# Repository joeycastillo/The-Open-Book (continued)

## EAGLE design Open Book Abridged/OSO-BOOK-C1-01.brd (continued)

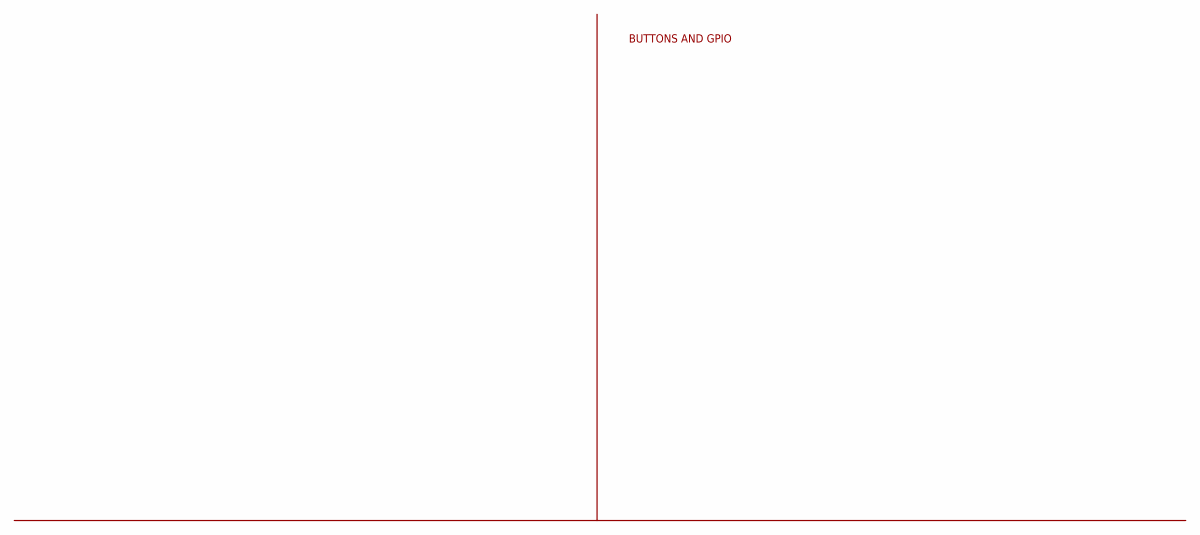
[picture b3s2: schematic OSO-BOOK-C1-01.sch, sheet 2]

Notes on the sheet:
BUTTONS AND GPIO

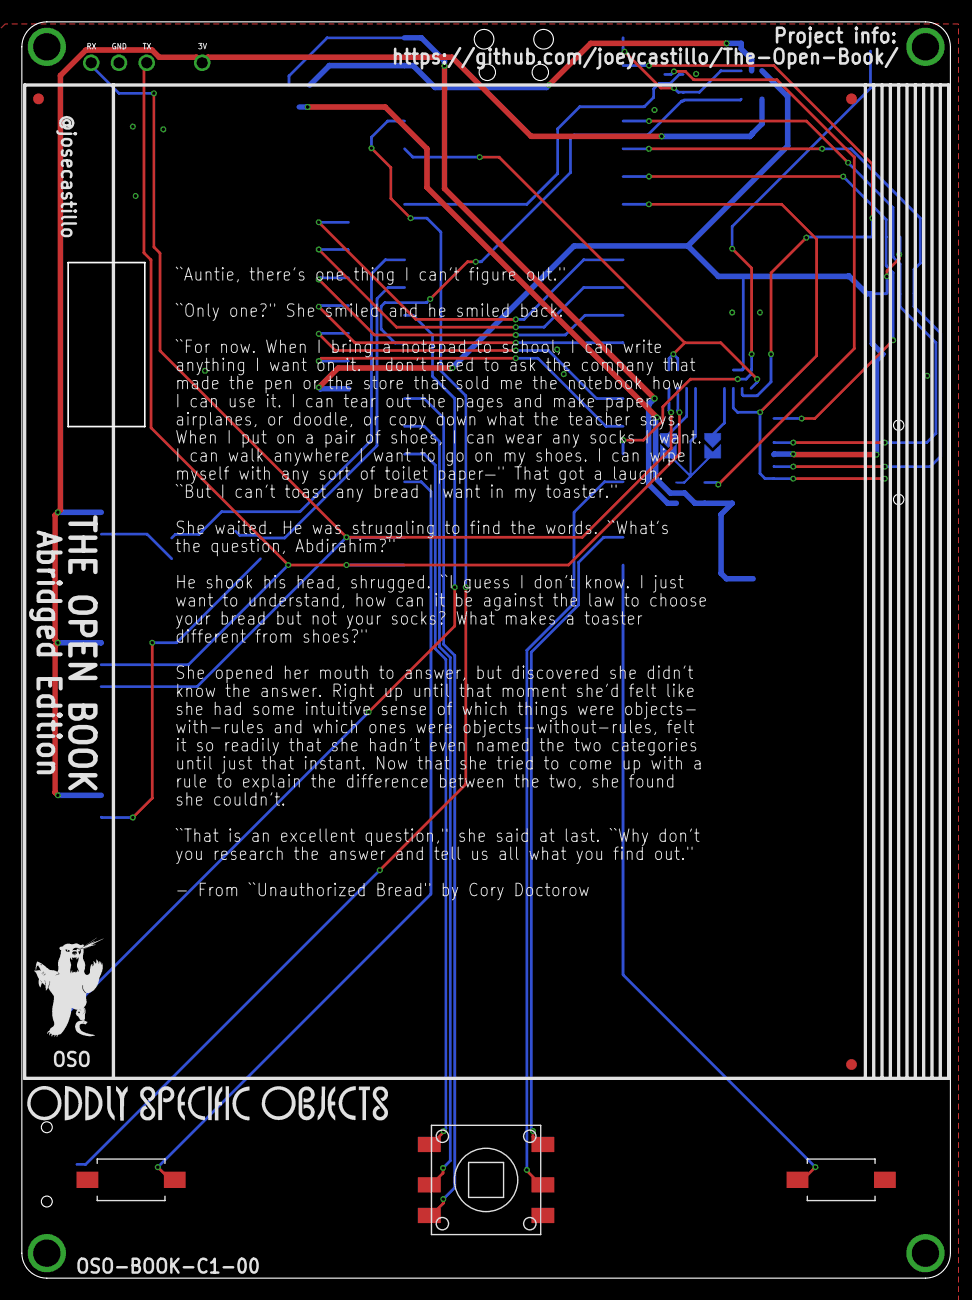
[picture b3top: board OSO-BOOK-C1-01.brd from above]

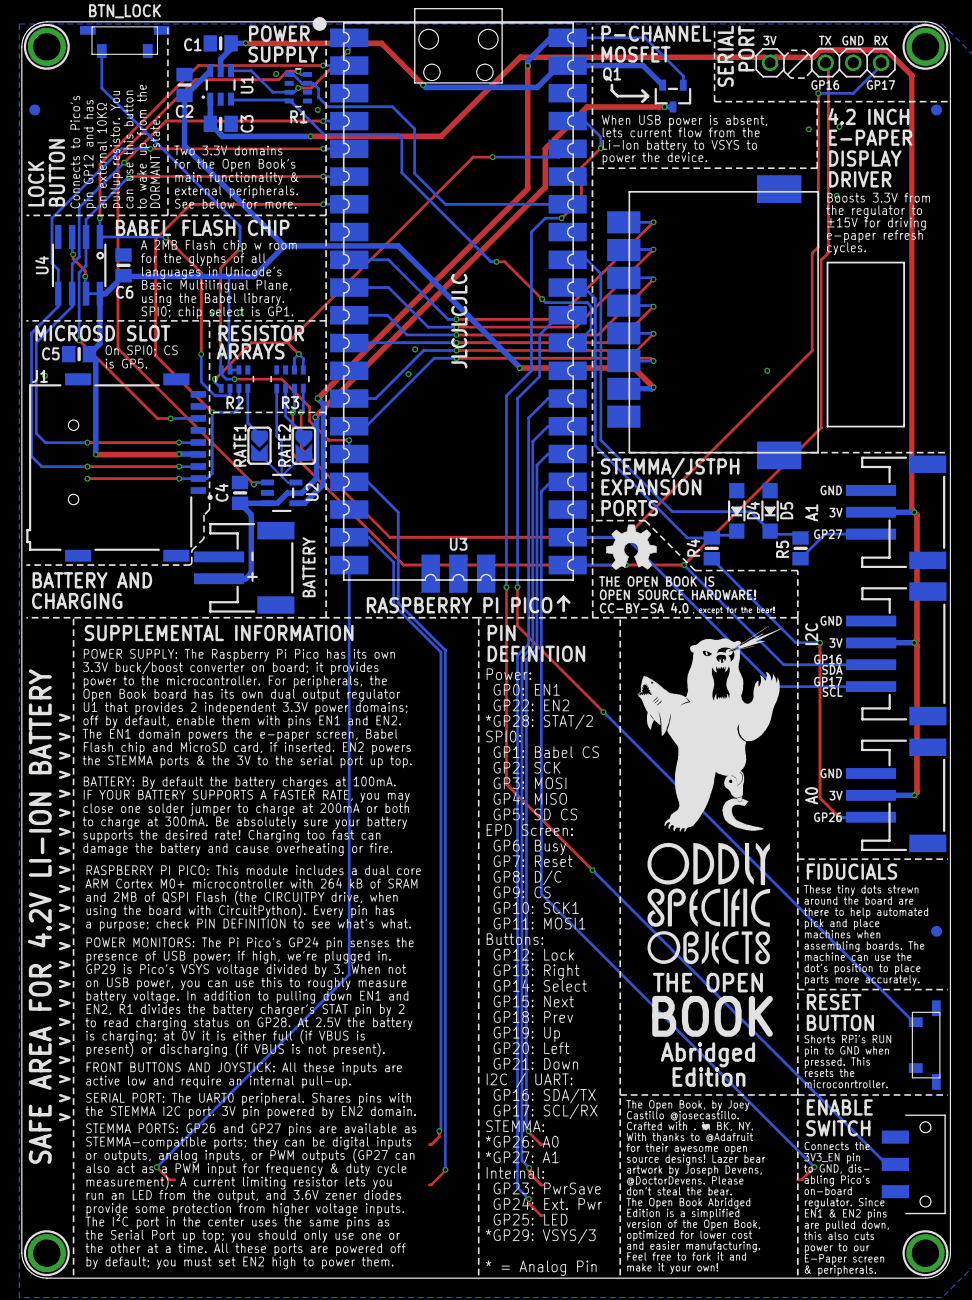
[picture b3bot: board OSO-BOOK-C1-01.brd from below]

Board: 2 copper layers, 85.0 x 115.0 mm, 49 parts (41 on the bottom side), 41 nets.

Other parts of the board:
U$45: OSO_WORDMARK_125X1300MIL_1000DPI
U$47: OSO_BEAR_525X750MIL_1000DPI
U$49: OSO_WORDMARK_THREELINE_450MIL_1000DPI
U$65: OSO_BEAR_250X360MIL_1000DPI

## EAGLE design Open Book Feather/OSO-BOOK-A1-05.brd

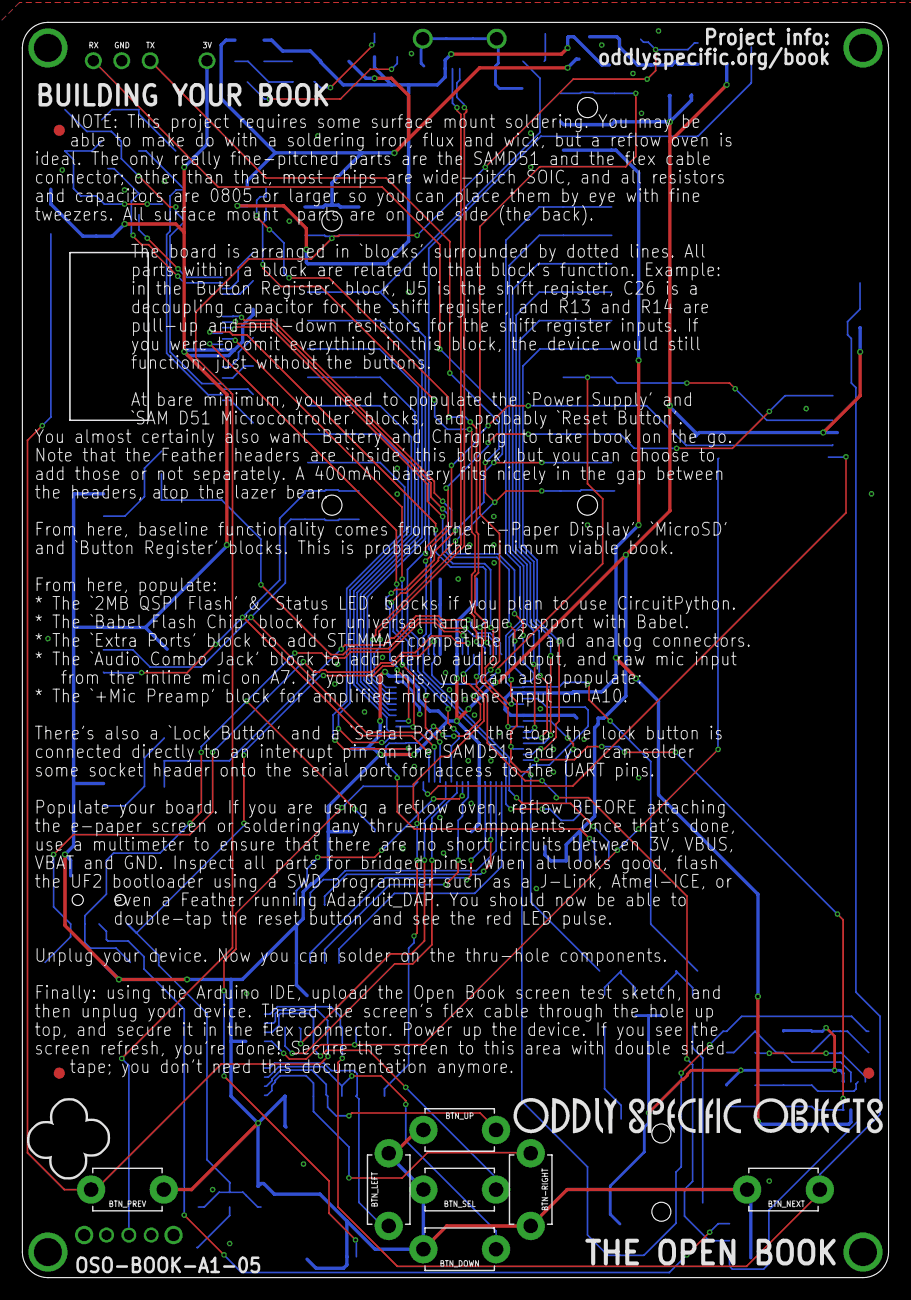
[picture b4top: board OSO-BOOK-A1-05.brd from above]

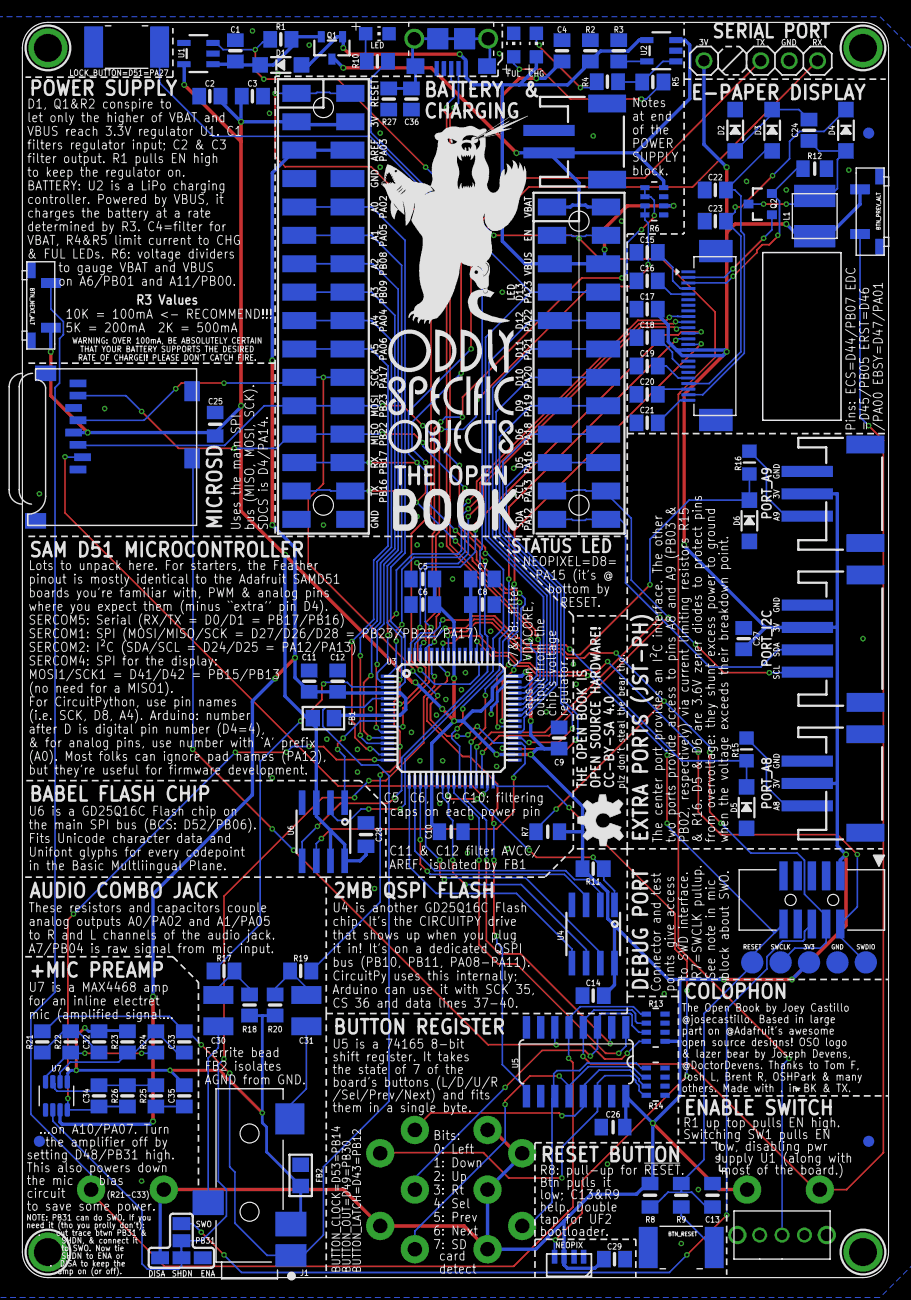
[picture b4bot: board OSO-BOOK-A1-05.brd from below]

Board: 2 copper layers, 77.5 x 112.3 mm, 130 parts (117 on the bottom side), 100 nets.

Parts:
BTN-RIGHT: TACT_PANA-EVQ
BTN_DOWN: TACT_PANA-EVQ
BTN_LEFT: TACT_PANA-EVQ
BTN_LOCK: BTN_CK_KSS
BTN_NEXT: TACT_PANA-EVQ
BTN_PREV: TACT_PANA-EVQ
BTN_RESET: BTN_CK_KSS
BTN_SEL: TACT_PANA-EVQ
BTN_UP: TACT_PANA-EVQ
C1, C2, C4, C11: 10µF; 0805-NO
C3, C9, C12, C14, C15, C16, C17, C29: 1uF; 0805-NO
C5, C7, C25: 10uF; 0805_10MGAP
C6, C8, C10, C26, C28: 1uF; 0805_10MGAP
C13: 0.1uF; 0805_10MGAP
C18, C19, C20, C21, C22, C23: 1uF/25V; 0805-NO
C24: 4.7uF/25V; 0805-NO
C27, C35: 10uF; 0805-NO
C30, C31: 100uF; C1210
C32: 0.1µF; 0805-NO
C33: 0.01uF; 0805-NO
C34: 100pF; 0805-NO
C36: 4.5nF; 0805-NO
CHG: AMBER; CHIP-LED0805
D1: MBR120; SOD-123
D2, D3, D4: MBR0530; SOD-123
D5, D6: 3.6V; SOD-123
DNP_NEXT_ALT: SPST_TACTILE_SWITCHRA; TL3330AF130QG
DNP_PREV_ALT: SPST_TACTILE_SWITCHRA; TL3330AF130QG
FB1, FB2: Ferrite; 0805
FID1, FID2, FID3, FID4, FID5, FID6: FIDUCIAL_1MM
FUL: GREEN; CHIP-LED0805
GOLD_ORB_SM1: OSHWLOGOLOGO5MM; OSHW_5MM
J1: SJ-43514-SMT; CUI_SJ-43514-SMT
J2: 10118193-0001LF; FCI_10118193-0001LF
JP1: 1X03
JP2: 1X01
L1: 10uH; MICROBUILDER_INDUCTOR_4X4MM_NR401_BIGPADS
LED: RED; CHIP-LED0805
MICROSD: MICROSD
MS1: FEATHERWING_SMTDUAL; FEATHERWING_SMT2
NEOPIX: WS2812B_4020
PORT_A8, PORT_A9: JST PH 3; JSTPH3
PORT_I2C: JST PH 4; JSTPH4
Q1: DMG341; SOT23-R
Q2: IRLML0100; SOT23-3
R1, R3: 10K; 0805-NO
R2, R11, R26: 100K; 0805-NO
R4, R5, R10, R21, R22, R25: 1K; 0805-NO
R6, R13, R14: 100K; EXBV8V
R7, R8: 10K; 0805_10MGAP
R9: 100; 0805_10MGAP
R12: 0.47ohm; 0805_10MGAP
R15, R16: 1K; _0805MP
R17, R18, R19, R20: 100; 0805-NO
R23, R24, R27: 1M; 0805-NO
SJ1: SOLDERJUMPER_FIVEWAY
SW1: SPDT_SWITCH; A10767
TP1, TP2, TP6, TP7, TP8: TESTPOINT_ROUND_2MM_NO
U1: AP2112-3.3; SOT23-5
U2: MCP73831T-2ACI/OT; SOT23-5
U3: ATSAMD51J64-TQFP(10X10); TQFP64-10X10
U4: GD25Q16C (or GD25Q32C); SOIC8_150MIL
U5: 74AC165D; SO16
U6: GD25Q16C (or GD25Q32C); MICROBUILDER_SOIC8_150MIL
U7: MAX4468EKAT; SOT65P280X145-8N
U$1, U$4, U$5, U$7: MOUNTINGHOLE2.5; MOUNTINGHOLE_2.5_PLATED
U$2: WAVESHARE_4_2_INCH_EINK_DISPLAY; EINK_DISPLAY_4_2IN
U$45: OSO_WORDMARK_125X1300MIL_1000DPI
U$47: OSO_BEAR_525X750MIL_1000DPI
U$48: OSO-LOGO-250MIL
U$49: OSO_WORDMARK_THREELINE_450MIL_1000DPI
X1: JSTPH; JSTPH2
X2: 2x5 0.05" SWD; 2X05_1.27MM_BOX_POSTS

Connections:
!RESET: C13.2, MS1.1, MS1.1', R8.2, R9.2, TP8.P$1, U3.52, X2.10
+3V3: BTN-RIGHT.P$2, BTN_DOWN.P$2, BTN_LEFT.P$2, BTN_NEXT.P$2, BTN_PREV.P$2, BTN_SEL.P$2, BTN_UP.P$2, C2.1, C3.1, C5.1, C6.1, C9.1, C10.1, C14.1, C17.2, C25.1, C26.1, C27.1, C28.1, C29.1, DNP_NEXT_ALT.P$2, DNP_PREV_ALT.P$2, FB1.1, JP2.1, L1.P$1, MICROSD.4, MS1.2, MS1.2', NEOPIX.2, PORT_A8.2, PORT_A9.2, PORT_I2C.2, R7.1, R8.1, R11.1, R13.5, SJ1.3, TP2.P$1, U1.5, U3.21, U3.34, U3.48, U3.56, U4.8, U5.16, U6.3, U6.7, U6.8, U$2.15, U$2.16, X2.1
A0: MS1.5, MS1.5', R17.2, U3.3
A1: MS1.6, MS1.6', R19.2, U3.14
A2: MS1.7, MS1.7', U3.11
A3: MS1.8, MS1.8', U3.12
A4: MS1.9, MS1.9', U3.13
A5: MS1.10, MS1.10', U3.15
A6_BATMON: R6.1, R6.2, U3.62
A7_MIC: C33.1, J1.1, R21.1, U3.5
A8_: PORT_A8.3, R15.1
A9_: PORT_A9.3, R16.1
A10_MICAMP: C34.1, R26.2, U3.16, U7.8
A11_BUSMON: R6.3, R6.4, U3.61
AGND: C32.2, C35.2, FB2.1, J1.4, R18.1, R20.1, R23.1, U7.1
AUDIO_LEFT: C31.2, J1.2
AUDIO_RIGHT: C30.2, J1.3
AVCC: C11.1, C12.1, FB1.2, MS1.3, MS1.3', U3.4, U3.8, U7.7
BUTTON0: BTN_LEFT.P$1, R14.1, U5.11
BUTTON1: BTN_DOWN.P$1, R14.2, U5.12
BUTTON2: BTN_UP.P$1, R14.3, U5.13
BUTTON3: BTN-RIGHT.P$1, R14.4, U5.14
BUTTON4: BTN_SEL.P$1, R13.3, U5.3
BUTTON5: BTN_PREV.P$1, DNP_PREV_ALT.P$1, R13.2, U5.4
BUTTON6: BTN_NEXT.P$1, DNP_NEXT_ALT.P$1, R13.1, U5.5
BUTTON7: MICROSD.CD2, R13.4, U5.6
BUTTONLOCK: BTN_LOCK.P$1, U3.51
BUTTON_CLK: U3.27, U5.2
BUTTON_LATCH: U3.25, U5.1
BUTTON_OUT: U3.59, U5.9
D2_A8: D5.C, R15.2, U3.64
D3_A9: D6.C, R16.2, U3.63
D5: MS1.19, MS1.19', U3.35
D6: MS1.20, MS1.20', U3.37
D8_NEOPIX: NEOPIX.1, U3.32
D9: MS1.21, MS1.21', U3.38
D10: MS1.22, MS1.22', U3.41
D11: MS1.23, MS1.23', U3.42
D12: MS1.24, MS1.24', U3.43
D13: MS1.25, MS1.25', R10.1, U3.44
EINK_BUSY: U3.2, U$2.9
EINK_CS: U3.10, U$2.12
EINK_DC: U3.6, U$2.11
EINK_MOSI: U3.28, U$2.14
EINK_RST: U3.1, U$2.10
EINK_SCK: U3.26, U$2.13
EN: MS1.27, MS1.27', R1.1, SW1.P$2, U1.3
GDR: Q2.1, U$2.2
GND: BTN_LOCK.P$2, BTN_RESET.P$1, C1.2, C2.2, C3.2, C4.2, C5.2, C6.2, C7.2, C8.2, C9.2, C10.2, C11.2, C12.2, C13.1, C14.2, C15.1, C16.1, C17.1, C18.1, C19.1, C20.1, C21.1, C22.2, C23.2, C25.2, C26.2, C27.2, C28.2, C29.2, C36.2, D2.C, D5.A, D6.A, FB2.2, FUL.C, J2.5, JP1.2, LED.C, MICROSD.6, MICROSD.MT1, MICROSD.MT2, MS1.4, MS1.4', MS1.16, MS1.16', NEOPIX.4, PORT_A8.1, PORT_A9.1, PORT_I2C.1, R2.2, R3.2, R6.5, R6.7, R12.2, R13.6, R13.7, R13.8, R14.5, R14.6, R14.7, R14.8, R27.2, SJ1.4, SW1.P$3, TP1.P$1, U1.2, U2.2, U3.7, U3.22, U3.33, U3.47, U3.54, U4.4, U5.8, U5.10, U5.15, U6.4, U$2.8, U$2.17, X1.1, X2.3, X2.5
MICAMP_SHDN: SJ1.2, U7.6
MIC_BIAS_PWR: R22.2, R24.2, U7.4
MISO: MICROSD.7, MS1.13, MS1.13', U3.49, U6.2
MOSI: MICROSD.3, MS1.12, MS1.12', U3.50, U6.5
unnamed: BTN_RESET.P$2, R9.1
unnamed: C24.2, D2.A, D3.C
unnamed: C24.1, D4.A, L1.P$2, Q2.3
unnamed: CHG.C, R4.1
unnamed: LED.A, R10.2
unnamed: FUL.A, R5.1
unnamed: C31.1, R19.1, R20.2
unnamed: C32.1, R21.2, R22.1
unnamed: C33.2, R23.2, R24.1, U7.2
unnamed: C34.2, R25.1, R26.1, U7.3
unnamed: C35.1, R25.2
unnamed: C30.1, R17.1, R18.2
PB31_SWO_MICSHDN: SJ1.1, U3.60
PREVGH: C23.1, D4.C, U$2.21
PREVGL: C22.1, D3.A, U$2.23
PROG: R3.1, U2.5
QSPI_CS: R11.2, U3.24, U4.1
QSPI_DATA[0]: U3.17, U4.5
QSPI_DATA[1]: U3.18, U4.2
QSPI_DATA[2]: U3.19, U4.3
QSPI_DATA[3]: U3.20, U4.7
QSPI_SCK: U3.23, U4.6
RESE: Q2.2, R12.1, U$2.3
RX: JP1.3, MS1.14, MS1.14', U3.40
SCK: MICROSD.5, MS1.11, MS1.11', U3.36, U6.6
SCL: MS1.18, MS1.18', PORT_I2C.4, U3.30
SDA: MS1.17, MS1.17', PORT_I2C.3, U3.29
SDCS: MICROSD.2, U3.31
SHIELD: C36.1, J2.S1, J2.S2, J2.S3, J2.S4, J2.S5, J2.S6, R27.1
STAT: R4.2, R5.2, U2.1
SWCLK: R7.2, TP6.P$1, U3.57, X2.4
SWDIO: TP7.P$1, U3.58, X2.2
SWO: SJ1.5, X2.6
TX: JP1.1, MS1.15, MS1.15', U3.39
UNIFONT_CS: U3.9, U6.1
USB_N: J2.2, U3.45
USB_P: J2.3, U3.46
V+: C1.1, D1.C, Q1.2, R1.2, U1.1
VBAT: C4.1, MS1.28, MS1.28', Q1.3, R6.8, U2.3, X1.2
VBUS: CHG.A, D1.A, J2.1, MS1.26, MS1.26', Q1.1, R2.1, R6.6, U2.4
VCOM: C21.2, U$2.24
VDD: C18.2, U$2.18
VDDCORE2: C7.1, C8.1, U3.53
VGH: C16.2, U$2.5
VGL: C15.2, U$2.4
VSH: C19.2, U$2.20
VSL: C20.2, U$2.22

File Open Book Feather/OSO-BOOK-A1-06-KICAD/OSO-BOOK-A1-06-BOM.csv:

Reference, Quantity, Value, Footprint, Datasheet
BTN-RIGHT1 BTN_DOWN1 BTN_LEFT1 BTN_NEXT1 BTN_PREV1 BTN_SEL1 BTN_UP1 ,7,"SWITCH_PUSHBUTTONEVQ-PE","OSO-BOOK-A1-06:TACT_PANA-EVQ",""
BTN_LOCK1 BTN_RESET1 DNP_NEXT_ALT1 DNP_PREV_ALT1 ,4,"SPST_TACTILE_SWITCHRA","OSO-BOOK-A1-06:TL3330AF130QG",""
C1 C11 C2 C4 ,4,"10µF","OSO-BOOK-A1-06:0805-NO",""
C13 ,1,"0.1uF","OSO-BOOK-A1-06:0805_10MGAP",""
C18 C19 C20 C21 C22 C23 ,6,"1uF/25V","OSO-BOOK-A1-06:0805-NO",""
C24 ,1,"4.7uF/25V","OSO-BOOK-A1-06:0805-NO",""
C27 C35 ,2,"10uF","OSO-BOOK-A1-06:0805-NO",""
C12 C14 C15 C16 C17 C29 C3 C9 ,8,"1uF","OSO-BOOK-A1-06:0805-NO",""
C30 C31 ,2,"100uF","OSO-BOOK-A1-06:C1210",""
C32 ,1,"0.1µF","OSO-BOOK-A1-06:0805-NO",""
C33 ,1,"0.01uF","OSO-BOOK-A1-06:0805-NO",""
C34 ,1,"100pF","OSO-BOOK-A1-06:0805-NO",""
C36 ,1,"4.5nF","OSO-BOOK-A1-06:0805-NO",""
C25 C5 C7 ,3,"10uF","OSO-BOOK-A1-06:0805_10MGAP",""
C10 C26 C28 C6 C8 ,5,"1uF","OSO-BOOK-A1-06:0805_10MGAP",""
CHG1 ,1,"AMBER","OSO-BOOK-A1-06:CHIP-LED0805",""
D1 ,1,"MBR120","OSO-BOOK-A1-06:SOD-123",""
D2 D3 D4 ,3,"MBR0530","OSO-BOOK-A1-06:SOD-123",""
D5 D6 ,2,"3.6V","OSO-BOOK-A1-06:SOD-123",""
FB1 FB2 ,2,"Ferrite","OSO-BOOK-A1-06:0805",""
FID1 FID2 FID3 FID4 FID5 FID6 ,6,"FIDUCIAL_1MM","OSO-BOOK-A1-06:FIDUCIAL_1MM",""
FUL1 ,1,"GREEN","OSO-BOOK-A1-06:CHIP-LED0805",""
GOLD_ORB_SM1 ,1,"OSHWLOGOLOGO5MM","OSO-BOOK-A1-06:OSHW_5MM",""
J1 ,1,"SJ-43514-SMT","OSO-BOOK-A1-06:CUI_SJ-43514-SMT",""
J2 ,1,"10118193-0001LF","OSO-BOOK-A1-06:FCI_10118193-0001LF",""
JP1 ,1,"PINHD-1X3","OSO-BOOK-A1-06:1X03",""
JP2 ,1,"PINHD-1X1","OSO-BOOK-A1-06:1X01",""
L1 ,1,"10uH","OSO-BOOK-A1-06:MICROBUILDER_INDUCTOR_4X4MM_NR401_BIGPADS",""
LED1 ,1,"RED","OSO-BOOK-A1-06:CHIP-LED0805",""
MICROSD1 ,1,"MICROSD","OSO-BOOK-A1-06:MICROSD",""
MS1 ,1,"FEATHERWING_SMTDUAL","OSO-BOOK-A1-06:FEATHERWING_SMT2",""
NEOPIX1 ,1,"WS2812B_4020","OSO-BOOK-A1-06:WS2812B_4020",""
PORT_A8 PORT_A9 ,2,"JST PH 3","OSO-BOOK-A1-06:JSTPH3",""
PORT_I2C1 ,1,"JST PH 4","OSO-BOOK-A1-06:JSTPH4",""
Q1 ,1,"DMG341","OSO-BOOK-A1-06:SOT23-R",""
Q2 ,1,"IRLML0100","OSO-BOOK-A1-06:SOT23-3",""
R1 R3 ,2,"10K","OSO-BOOK-A1-06:0805-NO",""
R12 ,1,"0.47ohm","OSO-BOOK-A1-06:0805_10MGAP",""
R15 R16 ,2,"1K","OSO-BOOK-A1-06:_0805MP",""
R11 R2 R26 ,3,"100K","OSO-BOOK-A1-06:0805-NO",""
R17 R18 R19 R20 ,4,"100","OSO-BOOK-A1-06:0805-NO",""
R23 R24 R27 ,3,"1M","OSO-BOOK-A1-06:0805-NO",""
R30 R31 R32 R33 ,4,"10K","OSO-BOOK-A1-06:_0805MP",""
R10 R21 R22 R25 R4 R5 ,6,"1K","OSO-BOOK-A1-06:0805-NO",""
R13 R14 R6 ,3,"100K","OSO-BOOK-A1-06:EXBV8V",""
R28 R29 R7 R8 ,4,"10K","OSO-BOOK-A1-06:0805_10MGAP",""
R9 ,1,"100","OSO-BOOK-A1-06:0805_10MGAP",""
SJ1 ,1,"SOLDERJUMPER_FIVEWAY","OSO-BOOK-A1-06:SOLDERJUMPER_FIVEWAY",""
SW1 ,1,"SPDT_SWITCH","OSO-BOOK-A1-06:A10767",""
TP1 TP2 TP6 TP7 TP8 ,5,"TESTPOINTROUND2MMNO","OSO-BOOK-A1-06:TESTPOINT_ROUND_2MM_NO",""
U$1 U$4 U$5 U$7 ,4,"MOUNTINGHOLE2.5","OSO-BOOK-A1-06:MOUNTINGHOLE_2.5_PLATED",""
U$2 ,1,"WAVESHARE_4_2_INCH_EINK_DISPLAY","OSO-BOOK-A1-06:EINK_DISPLAY_4_2IN",""
U1 ,1,"AP2112-3.3","OSO-BOOK-A1-06:SOT23-5",""
U2 ,1,"MCP73831T-2ACI/OT","OSO-BOOK-A1-06:SOT23-5",""
U3 ,1,"ATSAMD51J64-TQFP(10X10)","OSO-BOOK-A1-06:TQFP64-10X10",""
U4 ,1,"GD25Q16C","OSO-BOOK-A1-06:SOIC8_150MIL",""
U5 ,1,"74AC165D","OSO-BOOK-A1-06:SO16",""
U6 ,1,"GD25Q16C","OSO-BOOK-A1-06:MICROBUILDER_SOIC8_150MIL",""
U7 ,1,"MAX4468EKAT","OSO-BOOK-A1-06:SOT65P280X145-8N",""
X1 ,1,"JSTPH","OSO-BOOK-A1-06:JSTPH2",""
X2 ,1,"2x5 0.05" SWD","OSO-BOOK-A1-06:2X05_1.27MM_BOX_POSTS",""

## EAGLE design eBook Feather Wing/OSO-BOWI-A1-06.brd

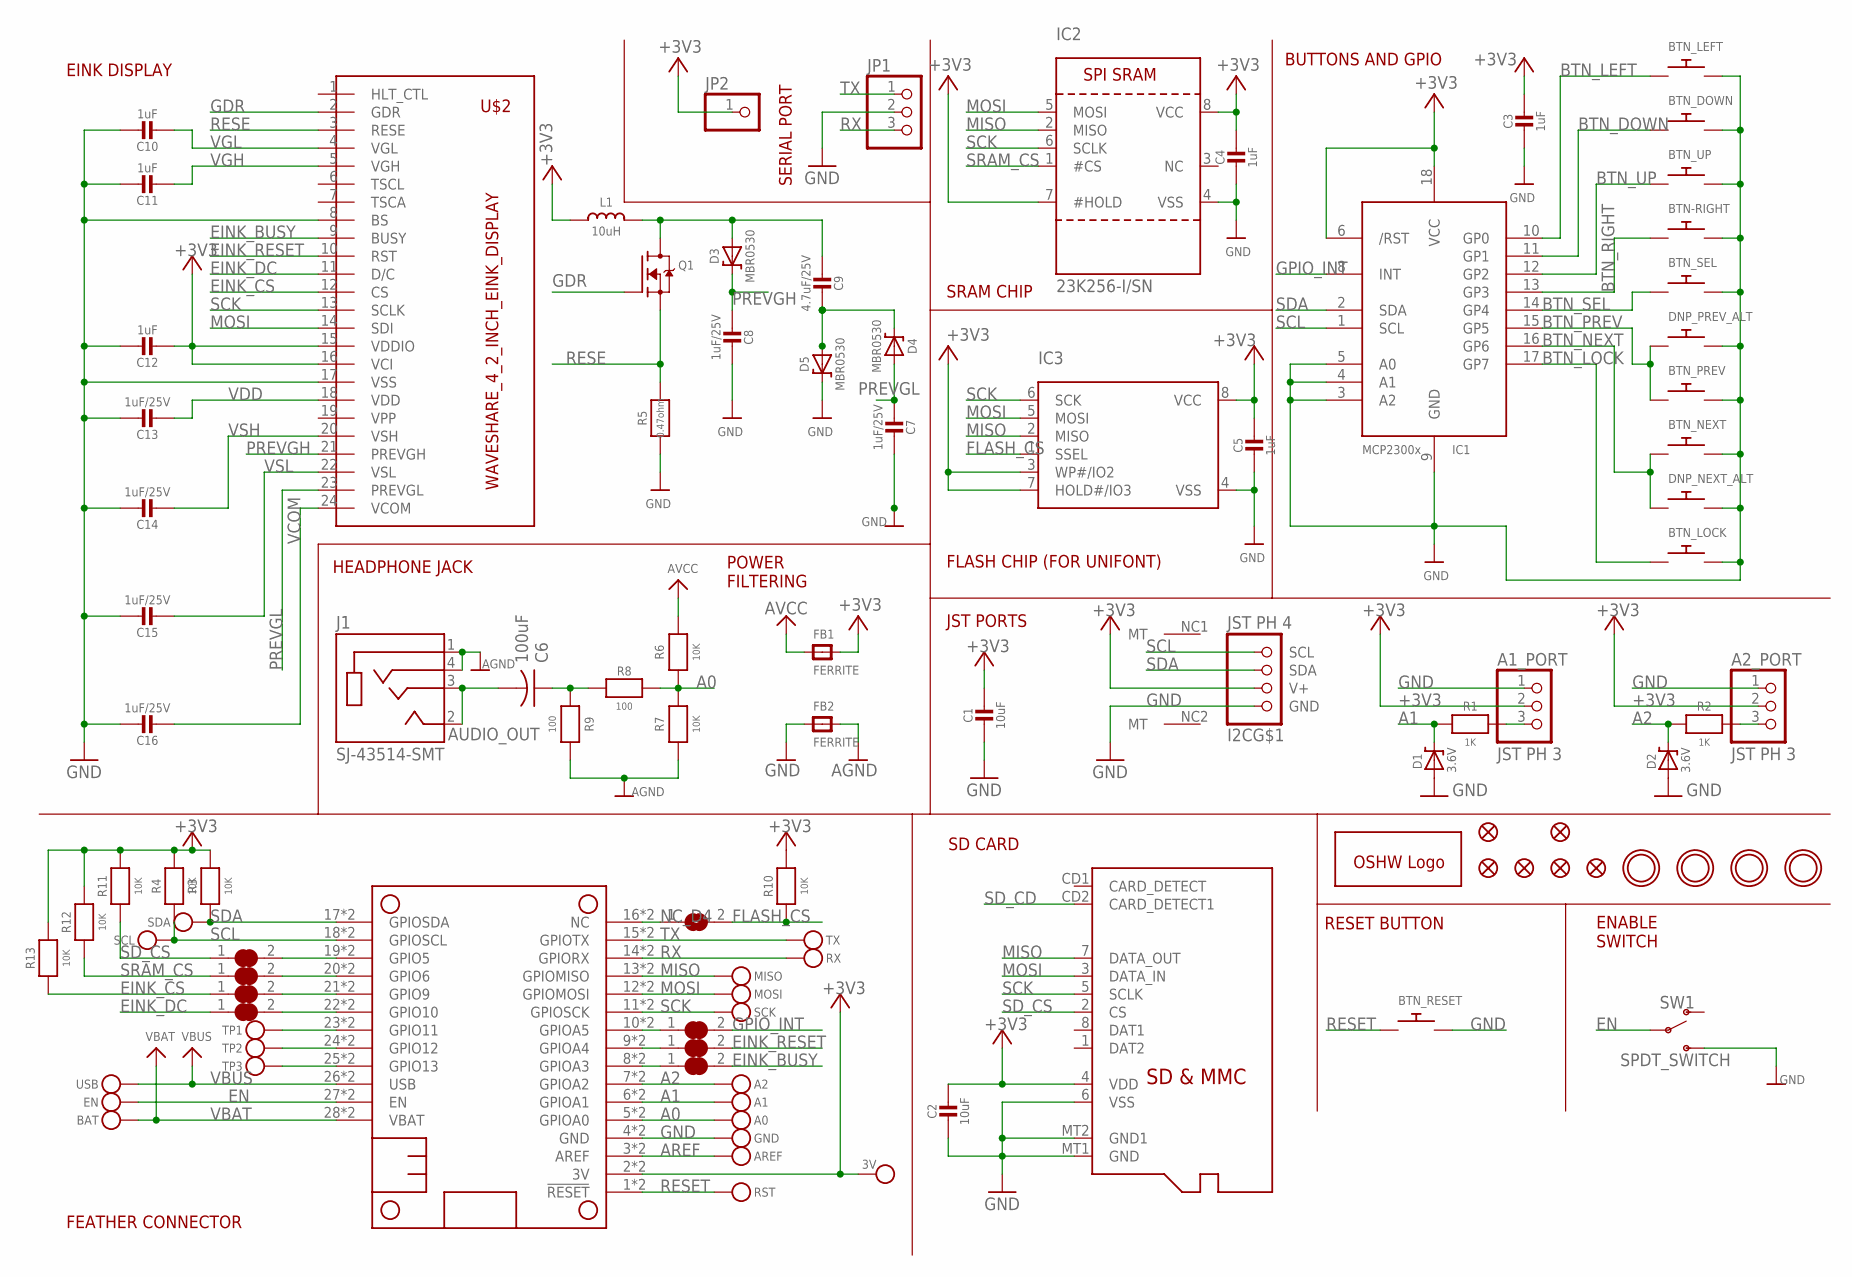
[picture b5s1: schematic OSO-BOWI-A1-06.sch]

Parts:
3V: MICROBUILDER_TESTPOINT1.5X2.0MM_NOCREAM; MICROBUILDER_PAD-1.5X2.0
A0, A1, A2: MICROBUILDER_TESTPOINT1.5X2.0MM_NOCREAM; MICROBUILDER_PAD-1.5X2.0
A1_PORT, A2_PORT: JST PH 3; JSTPH3
AREF: MICROBUILDER_TESTPOINT1.5X2.0MM_NOCREAM; MICROBUILDER_PAD-1.5X2.0
BAT: MICROBUILDER_TESTPOINT1.5X2.0MM_NOCREAM; MICROBUILDER_PAD-1.5X2.0
BCS: SOLDERJUMPER_OPEN
BTN-RIGHT: SWITCH_PUSHBUTTONEVQ-PE; TACT_PANA-EVQ
BTN_DOWN: SWITCH_PUSHBUTTONEVQ-PE; TACT_PANA-EVQ
BTN_LEFT: SWITCH_PUSHBUTTONEVQ-PE; TACT_PANA-EVQ
BTN_LOCK: SWITCH_PUSHBUTTONC&K_KSS; BTN_CK_KSS
BTN_NEXT: SWITCH_PUSHBUTTONEVQ-PE; TACT_PANA-EVQ
BTN_PREV: SWITCH_PUSHBUTTONEVQ-PE; TACT_PANA-EVQ
BTN_RESET: SWITCH_PUSHBUTTONC&K_KSS; BTN_CK_KSS
BTN_SEL: SWITCH_PUSHBUTTONEVQ-PE; TACT_PANA-EVQ
BTN_UP: SWITCH_PUSHBUTTONEVQ-PE; TACT_PANA-EVQ
C1: 10uF; 0805-NO
C2: 10uF; 0805_10MGAP
C3, C4, C5: 1uF; 0805_10MGAP
C6: 100uF; C1210
C7, C8, C13, C14, C15, C16: 1uF/25V; 0805-NO
C9: 4.7uF/25V; 0805-NO
C10, C11, C12: 1uF; 0805-NO
D1, D2: 3.6V; SOD-123
D3, D4, D5: MBR0530; SOD-123
DNP_NEXT_ALT: SPST_TACTILE_SWITCHRA; TL3330AF130QG
DNP_PREV_ALT: SPST_TACTILE_SWITCHRA; TL3330AF130QG
EBSY: MICROBUILDER_SOLDERJUMPER_CLOSED; MICROBUILDER_SOLDERJUMPER_CLOSEDWIRE
ECS: MICROBUILDER_SOLDERJUMPER_CLOSED; MICROBUILDER_SOLDERJUMPER_CLOSEDWIRE
EDC: MICROBUILDER_SOLDERJUMPER_CLOSED; MICROBUILDER_SOLDERJUMPER_CLOSEDWIRE
EN: MICROBUILDER_TESTPOINT1.5X2.0MM_NOCREAM; MICROBUILDER_PAD-1.5X2.0
ERST: MICROBUILDER_SOLDERJUMPER_CLOSED; MICROBUILDER_SOLDERJUMPER_CLOSEDWIRE
FB1, FB2: FERRITE; 0805
FID1, FID2, FID3, FID4, FID5, FID6: FIDUCIAL_1MM
GND: MICROBUILDER_TESTPOINT1.5X2.0MM_NOCREAM; MICROBUILDER_PAD-1.5X2.0
GOLD_ORB_SM1: OSHWLOGOLOGO5MM; OSHW_5MM
I2C: JST PH 4; JSTPH4
IC1: MCP23008/SO; SO18W
IC2: 23K256-I/SN; SOIC8_150MIL
IC3: MICROBUILDER_SPIFLASH_SOIC8; MICROBUILDER_SOIC8_150MIL
INT: MICROBUILDER_SOLDERJUMPER_CLOSED; MICROBUILDER_SOLDERJUMPER_CLOSEDWIRE
J1: SJ-43514-SMT; CUI_SJ-43514-SMT
JP1: PINHD-1X3; 1X03
JP2: PINHD-1X1; 1X01
L1: 10uH; MICROBUILDER_INDUCTOR_4X4MM_NR401_BIGPADS
MICROSD: MICROSD
MISO: MICROBUILDER_TESTPOINT1.5X2.0MM_NOCREAM; MICROBUILDER_PAD-1.5X2.0
MOSI: MICROBUILDER_TESTPOINT1.5X2.0MM_NOCREAM; MICROBUILDER_PAD-1.5X2.0
MS1: MICROBUILDER_FEATHERWING_SMTDUAL_NOLINES; MICROBUILDER_FEATHERWING_SMT2_NOLINES
Q1: IRLML0100; SOT23-3
R1, R2: 1K; _0805MP
R3, R4, R6, R7, R10, R11, R12, R13: 10K; _0805MP
R5: 0.47ohm; 0805_10MGAP
R8, R9: 100; _0805MP
RST: MICROBUILDER_TESTPOINT1.5X2.0MM_NOCREAM; MICROBUILDER_PAD-1.5X2.0
RX: MICROBUILDER_TESTPOINT1.5X2.0MM_NOCREAM; MICROBUILDER_PAD-1.5X2.0
SCK: MICROBUILDER_TESTPOINT1.5X2.0MM_NOCREAM; MICROBUILDER_PAD-1.5X2.0
SCL: MICROBUILDER_TESTPOINT1.5X2.0MM_NOCREAM; MICROBUILDER_PAD-1.5X2.0
SDA: MICROBUILDER_TESTPOINT1.5X2.0MM_NOCREAM; MICROBUILDER_PAD-1.5X2.0
SDCS: MICROBUILDER_SOLDERJUMPER_CLOSED; MICROBUILDER_SOLDERJUMPER_CLOSEDWIRE
SRCS: MICROBUILDER_SOLDERJUMPER_CLOSED; MICROBUILDER_SOLDERJUMPER_CLOSEDWIRE
SW1: SPDT_SWITCH; A10767
TP1, TP2, TP3: MICROBUILDER_TESTPOINT1.5X2.0MM_NOCREAM; MICROBUILDER_PAD-1.5X2.0
TX: MICROBUILDER_TESTPOINT1.5X2.0MM_NOCREAM; MICROBUILDER_PAD-1.5X2.0
U$1, U$4, U$5, U$7: MOUNTINGHOLE2.5; MOUNTINGHOLE_2.5_PLATED
U$2: WAVESHARE_4_2_INCH_EINK_DISPLAY; EINK_DISPLAY_4_2IN
USB: MICROBUILDER_TESTPOINT1.5X2.0MM_NOCREAM; MICROBUILDER_PAD-1.5X2.0

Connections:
+3V3: 3V.P$1, A1_PORT.2, A2_PORT.2, C1.1, C2.1, C3.1, C4.1, C5.1, C12.2, FB1.2, I2C.2 (V+), IC1.6 (/RST), IC1.18 (VCC), IC2.7 (#HOLD), IC2.8 (VCC), IC3.3 (WP#/IO2), IC3.7 (HOLD#/IO3), IC3.8 (VCC), JP2.1, L1.P$1 (1), MICROSD.4 (VDD), MS1.2 (3V), MS1.2' (3V), R3.1, R4.1, R10.1, R11.1, R12.1, R13.1, U$2.15 (VDDIO), U$2.16 (VCI)
A0: A0.P$1, MS1.5 (GPIOA0), MS1.5' (GPIOA0), R6.2, R7.1, R8.1
A1: A1.P$1, D1.C, MS1.6 (GPIOA1), MS1.6' (GPIOA1), R1.2
A1_: A1_PORT.3, R1.1
A2: A2.P$1, D2.C, MS1.7 (GPIOA2), MS1.7' (GPIOA2), R2.2
A2_: A2_PORT.3, R2.1
AGND: FB2.2, J1.1 (SLEEVE), J1.4 (RING2), R7.2, R9.1
AREF: AREF.P$1, MS1.3 (AREF), MS1.3' (AREF)
AUDIO_OUT: C6.2, J1.2 (TIP), J1.3 (RING1)
AVCC: FB1.1, R6.1
BTN_DOWN: BTN_DOWN.P$1, IC1.11 (GP1)
BTN_LEFT: BTN_LEFT.P$1, IC1.10 (GP0)
BTN_LOCK: BTN_LOCK.P$1, IC1.17 (GP7)
BTN_NEXT: BTN_NEXT.P$1, DNP_NEXT_ALT.P$1, IC1.16 (GP6)
BTN_PREV: BTN_PREV.P$1, DNP_PREV_ALT.P$1, IC1.15 (GP5)
BTN_RIGHT: BTN-RIGHT.P$1, IC1.13 (GP3)
BTN_SEL: BTN_SEL.P$1, IC1.14 (GP4)
BTN_UP: BTN_UP.P$1, IC1.12 (GP2)
EINK_BUSY: EBSY.2, U$2.9 (BUSY)
EINK_CS: ECS.1, R13.2, U$2.12 (CS)
EINK_DC: EDC.1, U$2.11 (D/C)
EINK_RESET: ERST.2, U$2.10 (RST)
EN: EN.P$1, MS1.27 (EN), MS1.27' (EN), SW1.P$2
FLASH_CS: BCS.2, IC3.1 (SSEL), R10.2
GDR: Q1.1 (G), U$2.2 (GDR)
GND: A1_PORT.1, A2_PORT.1, BTN-RIGHT.P$2, BTN_DOWN.P$2, BTN_LEFT.P$2, BTN_LOCK.P$2, BTN_NEXT.P$2, BTN_PREV.P$2, BTN_RESET.P$2, BTN_SEL.P$2, BTN_UP.P$2, C1.2, C2.2, C3.2, C4.2, C5.2, C7.2, C8.2, C10.1, C11.1, C12.1, C13.1, C14.1, C15.1, C16.1, D1.A, D2.A, D5.C, DNP_NEXT_ALT.P$2, DNP_PREV_ALT.P$2, FB2.1, GND.P$1, I2C.1 (GND), IC1.3 (A2), IC1.4 (A1), IC1.5 (A0), IC1.9 (GND), IC2.4 (VSS), IC3.4 (VSS), JP1.2, MICROSD.6 (VSS), MICROSD.MT1 (GND), MICROSD.MT2 (GND1), MS1.4 (GND), MS1.4' (GND), R5.2, SW1.P$3 (S), U$2.8 (BS), U$2.17 (VSS)
GPIO_INT: IC1.8 (INT), INT.2
MISO: IC2.2 (MISO), IC3.2 (MISO), MICROSD.7 (DATA_OUT), MISO.P$1, MS1.13 (GPIOMISO), MS1.13' (GPIOMISO)
MOSI: IC2.5 (MOSI), IC3.5 (MOSI), MICROSD.3 (DATA_IN), MOSI.P$1, MS1.12 (GPIOMOSI), MS1.12' (GPIOMOSI), U$2.14 (SDI)
unnamed: C6.1, R8.2, R9.2
unnamed: C9.2, D4.C, D5.A
unnamed: C9.1, D3.A, L1.P$2 (2), Q1.3 (D)
unnamed: MS1.25 (GPIO13), MS1.25' (GPIO13), TP3.P$1
unnamed: MS1.24 (GPIO12), MS1.24' (GPIO12), TP2.P$1
unnamed: MS1.23 (GPIO11), MS1.23' (GPIO11), TP1.P$1
NC_D4: BCS.1, MS1.16 (NC), MS1.16' (NC)
PREVGH: C8.1, D3.C, U$2.21 (PREVGH)
PREVGL: C7.1, D4.A, U$2.23 (PREVGL)
RESE: Q1.2 (S), R5.1, U$2.3 (RESE)
RESET: BTN_RESET.P$1, MS1.1 (!RESET), MS1.1' (!RESET), RST.P$1
RX: JP1.3, MS1.14 (GPIORX), MS1.14' (GPIORX), RX.P$1
SCK: IC2.6 (SCLK), IC3.6 (SCK), MICROSD.5 (SCLK), MS1.11 (GPIOSCK), MS1.11' (GPIOSCK), SCK.P$1, U$2.13 (SCLK)
SCL: I2C.4 (SCL), IC1.1 (SCL), MS1.18 (GPIOSCL), MS1.18' (GPIOSCL), R4.2, SCL.P$1
SDA: I2C.3 (SDA), IC1.2 (SDA), MS1.17 (GPIOSDA), MS1.17' (GPIOSDA), R3.2, SDA.P$1
SD_CD: MICROSD.CD2 (CARD_DETECT1)
SD_CS: MICROSD.2 (CS), R11.2, SDCS.1
SRAM_CS: IC2.1 (#CS), R12.2, SRCS.1
TX: JP1.1, MS1.15 (GPIOTX), MS1.15' (GPIOTX), TX.P$1
VBAT: BAT.P$1, MS1.28 (VBAT), MS1.28' (VBAT)
VBUS: MS1.26 (USB), MS1.26' (USB), USB.P$1
VCOM: C16.2, U$2.24 (VCOM)
VDD: C13.2, U$2.18 (VDD)
VGH: C11.2, U$2.5 (VGH)
VGL: C10.2, U$2.4 (VGL)
VSH: C14.2, U$2.20 (VSH)
VSL: C15.2, U$2.22 (VSL)
_EINK_BUSY: EBSY.1, MS1.8 (GPIOA3), MS1.8' (GPIOA3)
_EINK_CS: ECS.2, MS1.21 (GPIO9), MS1.21' (GPIO9)
_EINK_DC: EDC.2, MS1.22 (GPIO10), MS1.22' (GPIO10)
_EINK_RESET: ERST.1, MS1.9 (GPIOA4), MS1.9' (GPIOA4)
_GPIO_INT: INT.1, MS1.10 (GPIOA5), MS1.10' (GPIOA5)
_SD_CS: MS1.19 (GPIO5), MS1.19' (GPIO5), SDCS.2
_SRAM_CS: MS1.20 (GPIO6), MS1.20' (GPIO6), SRCS.2

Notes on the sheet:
FEATHER CONNECTOR
SD CARD
EINK DISPLAY
HEADPHONE JACK
RESET BUTTON
ENABLE SWITCH
POWER FILTERING
BUTTONS AND GPIO
JST PORTS
SRAM CHIP
FLASH CHIP (FOR UNIFONT)
SERIAL PORT

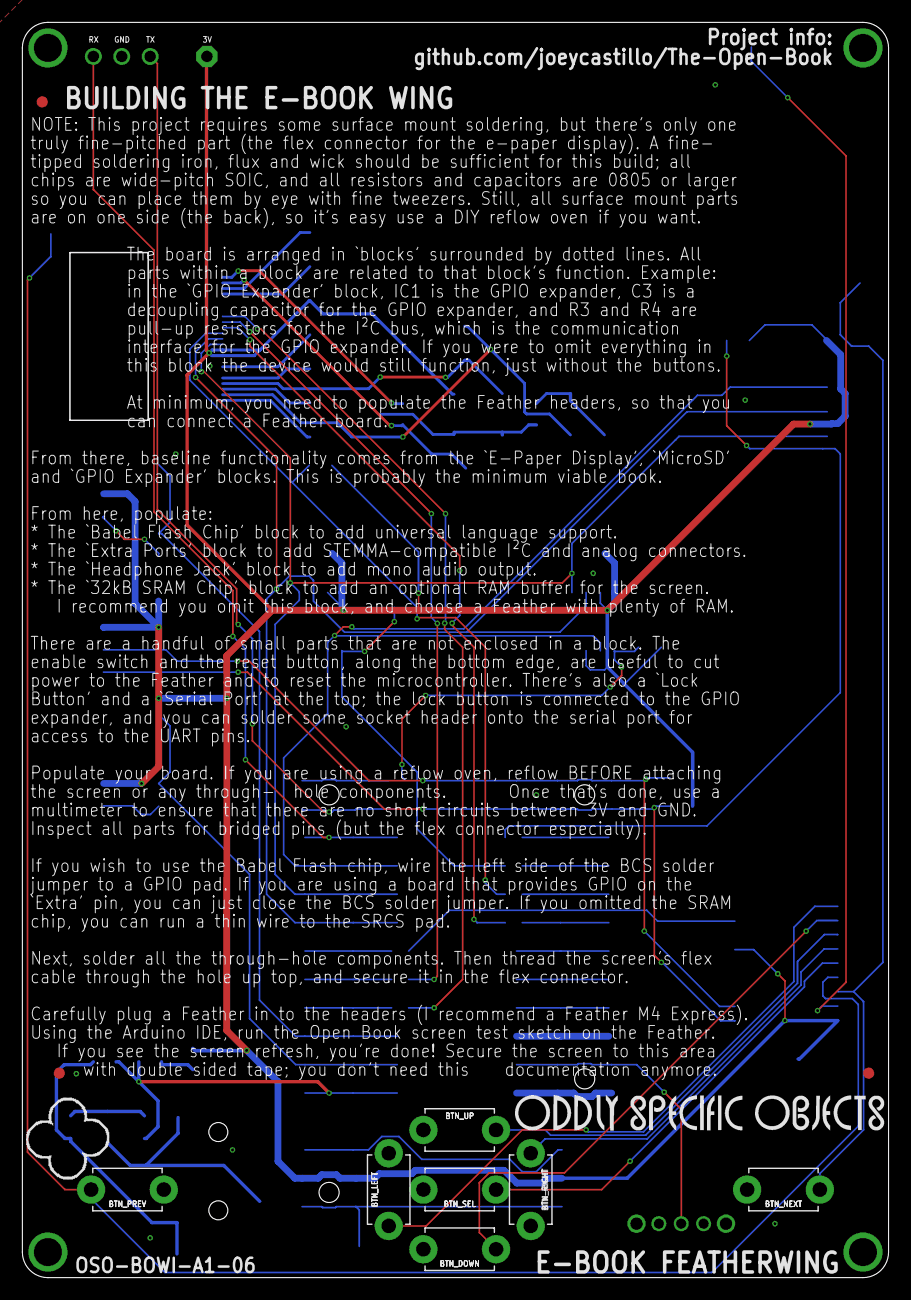
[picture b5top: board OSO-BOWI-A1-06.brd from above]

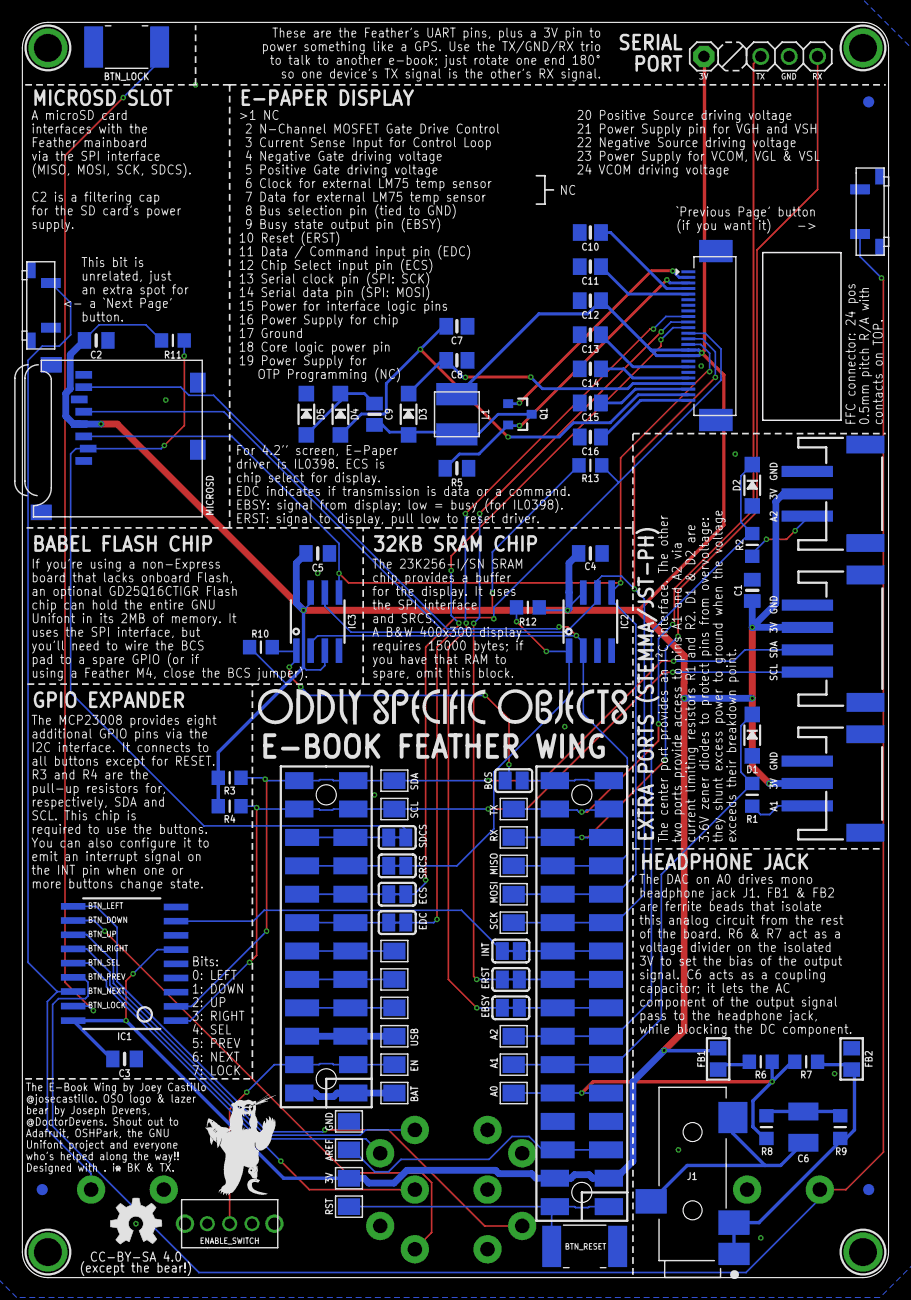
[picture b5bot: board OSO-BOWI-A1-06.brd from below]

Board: 2 copper layers, 77.5 x 112.3 mm, 105 parts (92 on the bottom side), 62 nets.

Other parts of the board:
U$11, U$13: OSO_WORDMARK_125X1300MIL_1000DPI
U$15: OSO_BEAR_250X360MIL_1000DPI
U$44: OSO_GRAPHIC
